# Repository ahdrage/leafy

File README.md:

# Leafy — DIY Wi-Fi Climate Controller for Nissan Leaf

**A DIY Nissan Leaf climate On/Off controller for home Wi-Fi.**

Leafy combines a custom ESP32-C3 board, a local web page and a printable enclosure. It requests climate operation over CAN; it does not carry or switch heater power. The intended profile is the **2013–2015 Leaf EV-CAN implementation**, subject to checking the actual vehicle and TCU configuration.

**Status: untested hardware prototype, Rev G.5 prepared for manufacture.** PCB production files and final component placement have been reviewed. Firmware builds and host tests pass, but no assembled Leafy has yet demonstrated heater control in a car. CAN transmission is disabled by default.

## Start here

| Goal | Documentation |
| --- | --- |
| Understand the project | [How it works](docs/OVERVIEW.md) |
| Build one | [Build guide](docs/BUILD-GUIDE.md) |
| Understand the decisions | [Development history](docs/DEVELOPMENT-HISTORY.md) |
| Inspect the current circuit | [G.5 design](hardware/rev-g/README.md), [schematic PDF](hardware/rev-g/exports/schematic.pdf), [KiCad project](hardware/rev-g/leaf-heat-v7.kicad_pro) |
| Buy components | [Parts and costs](docs/PARTS-AND-COSTS.md) |
| Order the PCB / partial assembly | [G.5 order guide](hardware/rev-g/ORDER-G5.md) |
| Build or test firmware | [Firmware instructions](firmware/leaf-heat/README.md) |
| Print the case | [Blender and STL files](enclosure/rev-g-v2/README.md) |
| Check the evidence | [Validation status](docs/VALIDATION.md) |

## Deliberately small scope

- **Heat on / Heat off** from a browser on the same home network.
- Wi-Fi only, external antenna, no SIM, subscription or cloud service.
- One CAN channel and the specified Nissan OVMS cable pinout.
- A 100 × 100 mm, four-layer PCB with generous hand-solder spacing.
- Factory assembly of **U1/U2/U4/U5/U6/L1**; **49 other components per board** are hand-soldered and the antenna plugs in.
- Independent low-battery cutoff, input damping and protected power/CAN interfaces.

Normal operation keeps Wi-Fi associated and retries after outages. **Battery protection cuts the board's power when voltage is too low**, so it becomes unreachable until the supply recovers. Availability also depends on the router and signal. Parked current and real-world reliability still need measurement.

The commands request the vehicle's climate function, not a particular heater element or temperature setpoint. The page reports requests, not independently verified heating.

## Thanks to OVMS

Leafy was inspired by the [Open Vehicle Monitoring System (OVMS)](https://www.openvehicles.com/). Its narrow Leaf wake-up and climate-command sequence is **derived from the OVMS Nissan Leaf implementation**, pinned to revision `85074a0ae7a983b308c6e2e081185492527ee073`.

Thank you to the OVMS authors and contributors for making this work available. The original MIT notice is retained in [OVMS-NOTICE.txt](firmware/leaf-heat/OVMS-NOTICE.txt). [Credits and provenance](CREDITS.md) explain the relationship and other sources. Leafy is an independent prototype, with no claimed OVMS or Nissan endorsement.

## Repository map

- `hardware/rev-g/`: current G.5 CAD, BOMs, manufacturing files, reviews and audit tools. The internal filename `leaf-heat-v7` is intentional.
- `firmware/leaf-heat/`: ESP-IDF firmware, settings template and 25 host tests.
- `enclosure/rev-g-v2/`: Blender source, STLs, renders and G.5 compatibility. Case renders retain their G.3 artwork provenance.
- `docs/`: project history, construction, costs, validation and publication notes.
- Earlier revisions and research: development history, **not current manufacturing instructions**. Always use matching G.5 files.

The public snapshot excludes personal supplier records, credentials, configured firmware images, downloaded toolchains and unrelated projects. Originals remain local. See [publication scope](docs/PUBLICATION.md).

## Licences

See [LICENSE.md](LICENSE.md) for the project licence boundaries and retained third-party notices.

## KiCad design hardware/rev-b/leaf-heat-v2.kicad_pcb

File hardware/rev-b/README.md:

> **Historical development record.** The current release is [Leafy G.5](../../README.md). Use this file for context, not current ordering or wiring instructions.

# Leaf Heat — Rev B

**Current engineering design. Four layers, 65 × 50 mm, 47 components. Not yet released for manufacture or vehicle installation.**

Open [leaf-heat-v2.kicad_pro](leaf-heat-v2.kicad_pro) in KiCad 10, then open PCB Editor. This revision replaces the two-layer Rev A layout. The circuit and heater-control purpose are unchanged; USB nets have been renamed to identify the differential pairs.

The board receives a command over home Wi-Fi and communicates with the Leaf through CAN. It does not carry heater power. Firmware, an enclosure and a tested Nissan ZE0 cable are still required.

## See the copper

Select **In1.Cu** in the PCB Editor's Layers panel and use **Show filled areas in zones**. Press **B** to refill after edits. That layer is the ground reference; there are no routed tracks on it. Copper is intentionally absent below the antenna and around non-ground holes/vias.

- [Top copper and components](exports/top.png)
- [Dedicated ground layer](exports/ground.png)
- [Internal power layer](exports/power.png)
- [Bottom copper](exports/bottom.png)
- [Component placement drawing](exports/placement.png)

## What changed

- Ground now has a dedicated internal layer plus connected surface copper. There are 87 separate ground vias, in addition to the thermal holes incorporated into footprints.
- Supply distribution uses copper areas and the internal power layer. Short, deliberately sized tracks still connect local parts.
- The regulator's bypass, bootstrap, local supply and feedback components have been regrouped. The feedback sense route comes from the output capacitor bank and stays away from the switching node.
- USB uses a parallel pair, short protection-device connections and resistors close to the controller. Both main copper paths measure approximately 40.991 mm. The main connector-to-controller paths have no vias; the USB-C duplicated-contact bridges have four local data vias and nearby ground return vias.
- Trace widths are selected by purpose. Making every trace the same width would make this design worse.

Read the [point-by-point review](LAYOUT-REVIEW.md) for the evidence and remaining limitations.

## Verification

KiCad 10.0.6 reports **0 electrical-rule violations, 0 layout-rule violations, 0 unconnected items and 0 schematic mismatches**. No DRC exclusions were added. The separate geometry audit confirms ground beneath the main USB route, matched copper lengths, main-pair spacing and no routed tracks on either internal layer.

The USB target is **90 Ω differential ±10%**. The proposed 0.25 mm traces and 0.15 mm gap calculate to **95.62 Ω in KiCad's uncoated coupled-microstrip model**. The actual solder mask, etched copper and factory stackup must be checked by the manufacturer before production. This is not measured impedance.

## Files for review

The native project, schematic, board, `.kicad_dru`, local symbols and local footprints must stay together. [BOM](exports/BOM-PCBWay.csv) and [placement coordinates](exports/placements.csv) are updated for Rev B. `exports/fabrication-review/` contains all four copper layers and drill files. See [manufacturing notes](MANUFACTURING-NOTES.md).

The existing PCBWay price was for Rev A. **It is not a price for this four-layer board.** Ordering remains paused while the design is reviewed. A four-layer board can cost more; it adds no components or wiring to the finished box.

This review does not demonstrate USB operation, power stability, parked-battery consumption, automotive transient immunity or successful heater control. Those require an assembled prototype and the bench/vehicle checks in [LAYOUT-REVIEW.md](LAYOUT-REVIEW.md). The earlier development-board plan uses different pin assignments.

## Custom-board firmware connections

| Signal | ESP32-C3 GPIO | Notes |
|---|---:|---|
| CAN TX / RX | 4 / 5 | Internal TWAI controller; intended Leaf profile 500 kbit/s |
| CAN standby | 1 | High = standby, pulled high by R10 |
| Battery sense | 0 | ADC; VPWR × 47/1047, measured after input diode |
| USB presence | 3 | ADC; half VBUS, use hysteresis |
| Status LED | 7 | High lights LED |
| USB D− / D+ | 18 / 19 | Native programming interface |
| Boot straps | 2, 8, 9 | Pulled high; BOOT button pulls GPIO9 low |

Start firmware with CAN in standby. Do not replay a heat request after reset. Implement a stop deadline, bus-error handling and a tested low-battery sleep policy. There is no independent hardware battery cutoff. USB and vehicle grounds are common; disconnect the vehicle during initial bench programming.

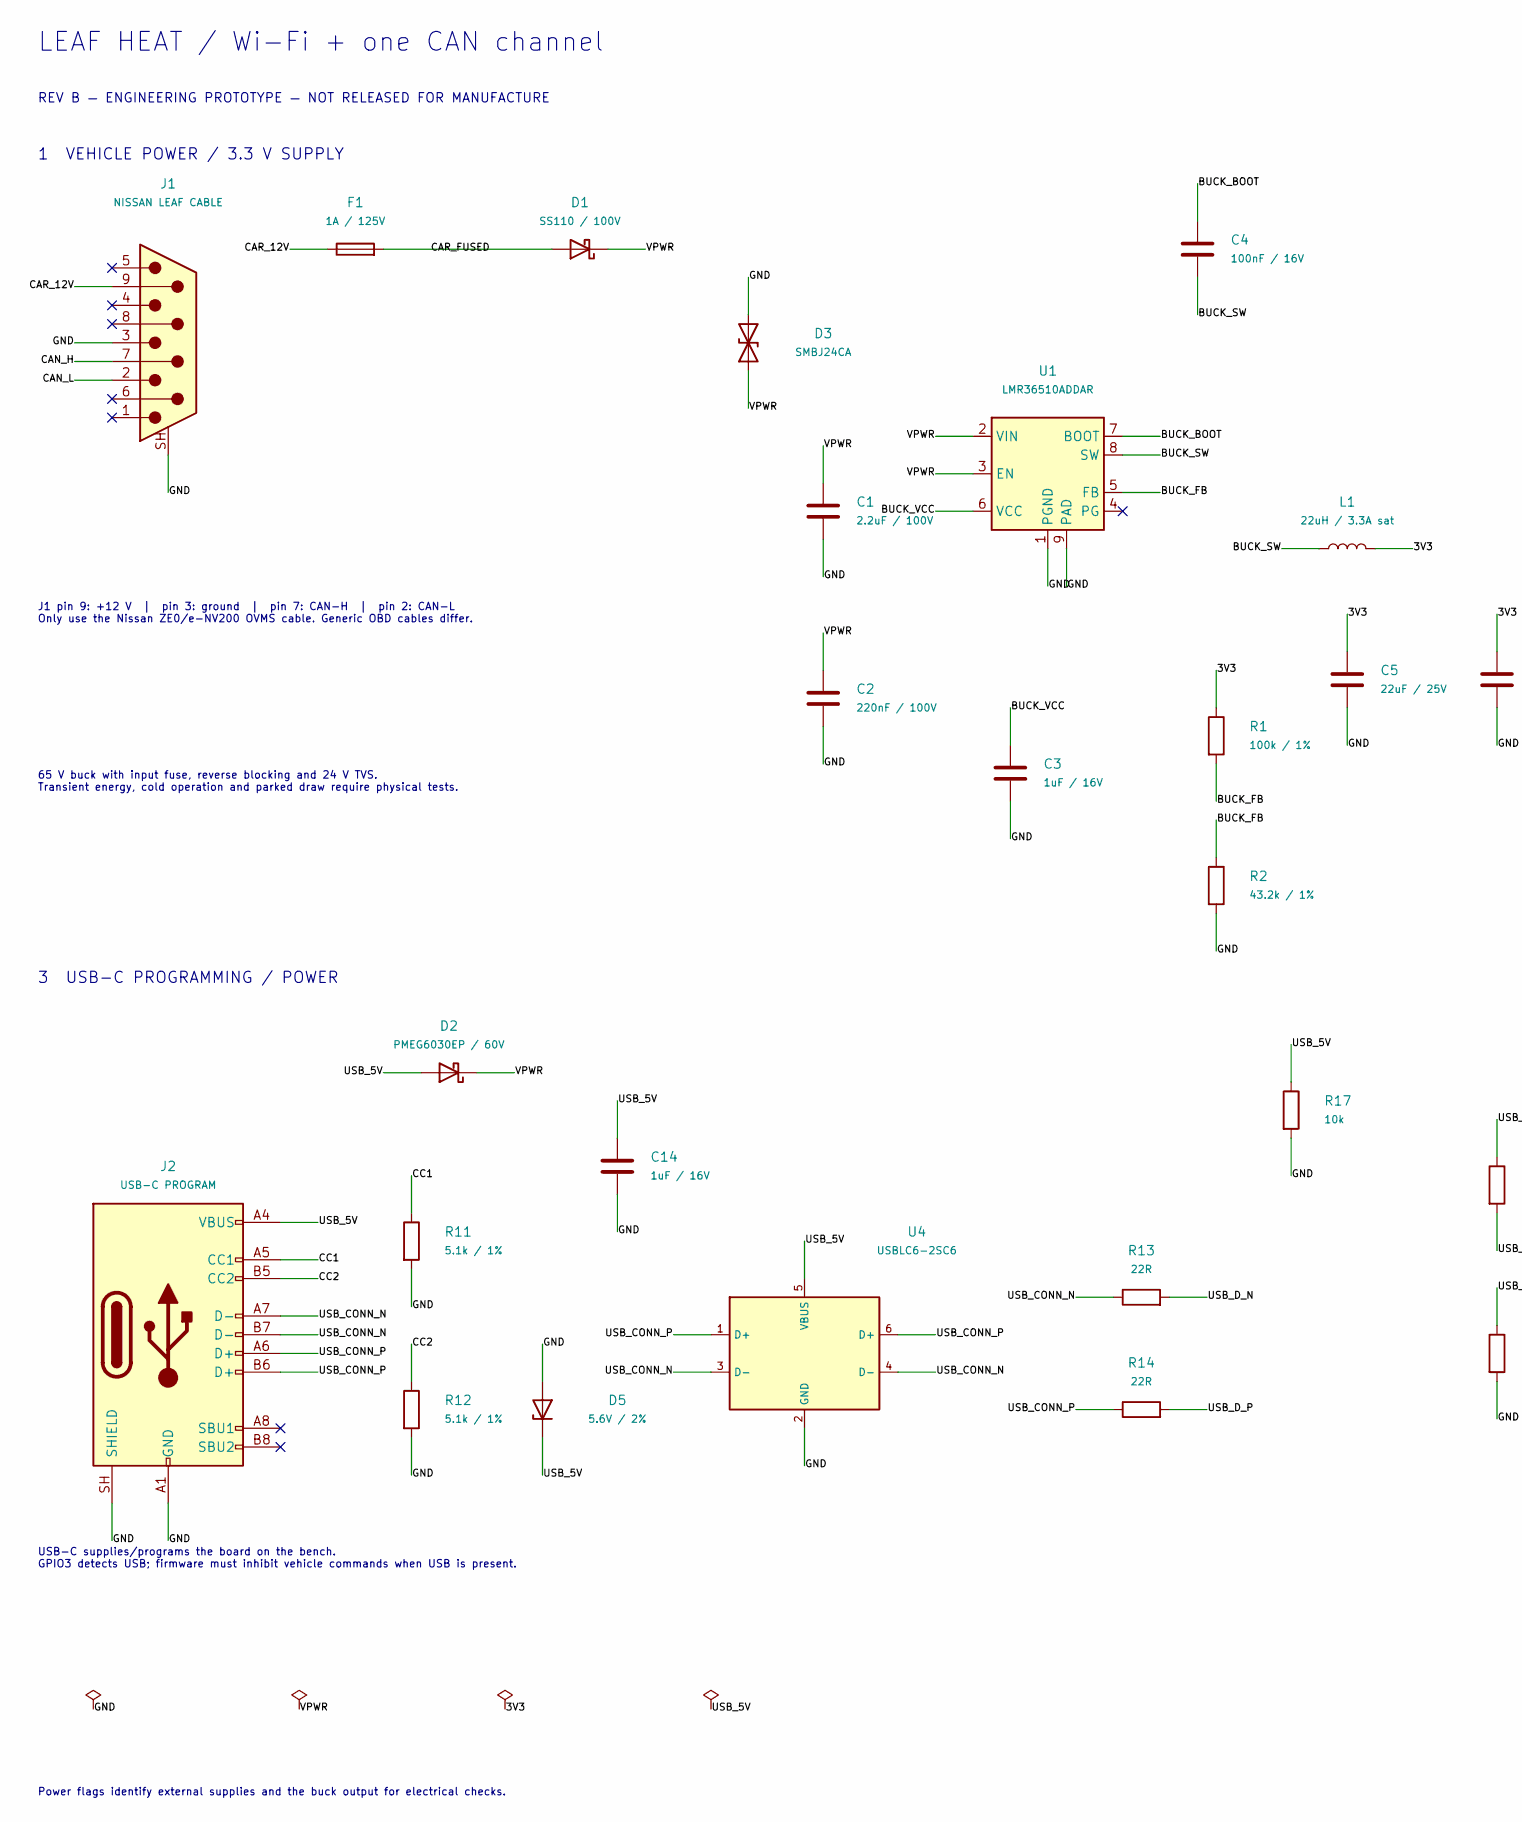
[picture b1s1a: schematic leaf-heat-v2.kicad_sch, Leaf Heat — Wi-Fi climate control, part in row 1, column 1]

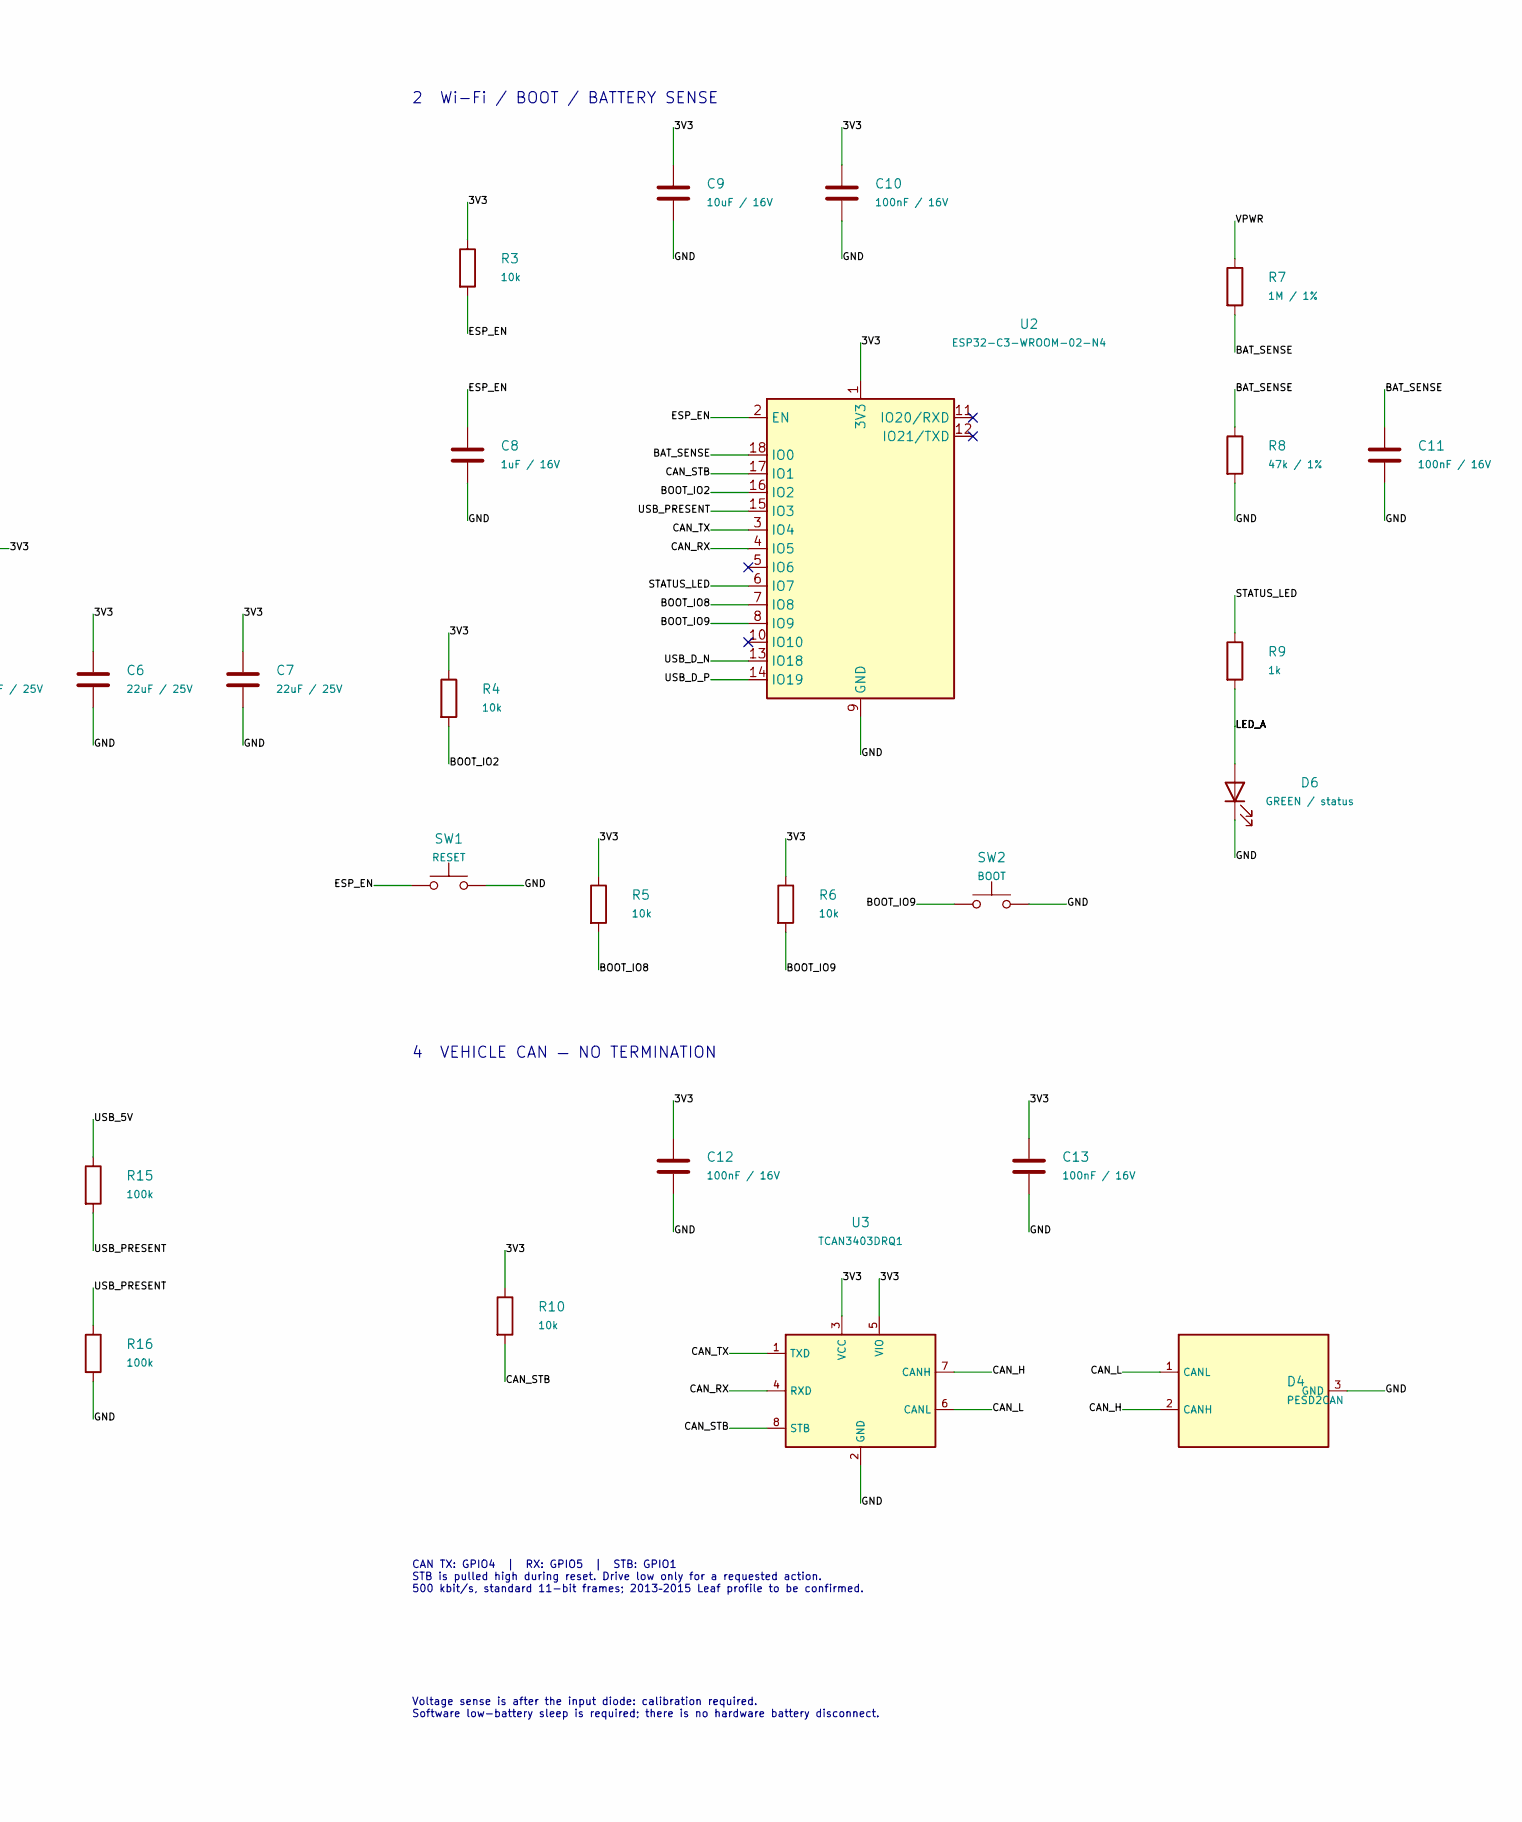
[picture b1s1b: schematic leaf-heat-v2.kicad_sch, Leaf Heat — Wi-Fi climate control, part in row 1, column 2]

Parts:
C1: 2.2uF / 100V; C_1210_3225Metric; MPN GRM32ER72A225KA35L
C2: 220nF / 100V; C_0805_2012Metric; MPN GRM21BR72A224KAC4L
C3, C8, C14: 1uF / 16V; C_0603_1608Metric; MPN GRM188R71C105KA12D
C4, C10, C11, C12, C13: 100nF / 16V; C_0603_1608Metric; MPN GRM188R71C104KA01D
C5, C6, C7: 22uF / 25V; C_1210_3225Metric; MPN GRM32ER71E226KE15L
C9: 10uF / 16V; C_0805_2012Metric; MPN GRM21BR71C106KE51L
D1: SS110 / 100V; D_SMA; MPN SS110-13-F
D2: PMEG6030EP / 60V; D_SOD-128; MPN PMEG6030EP,115
D3: SMBJ24CA; D_SMB; MPN SMBJ24CA
D4: PESD2CAN; SOT-23; MPN PESD2CAN,215
D5: 5.6V / 2%; D_SOD-123; MPN BZT52-B5V6X
D6: GREEN / status; LED_0603_1608Metric; MPN LTST-C190KGKT
F1: 1A / 125V; Fuse_Littelfuse-NANO2-451_453; MPN 0451001.MRL
J1: NISSAN LEAF CABLE; NorComp_182-009-113R531; MPN 182-009-113R531
J2: USB-C PROGRAM; USB_C_Receptacle_GCT_USB4105-xx-A_16P_TopMnt_Horizontal; MPN USB4105-GF-A
L1: 22uH / 3.3A sat; L_Bourns_SRN6045TA; MPN SRN6045TA-220M
R1: 100k / 1%; R_0603_1608Metric; MPN RC0603FR-07100KL
R2: 43.2k / 1%; R_0603_1608Metric; MPN RC0603FR-0743K2L
R3, R4, R5, R6, R10, R17: 10k; R_0603_1608Metric; MPN RC0603FR-0710KL
R7: 1M / 1%; R_0603_1608Metric; MPN RC0603FR-071ML
R8: 47k / 1%; R_0603_1608Metric; MPN RC0603FR-0747KL
R9: 1k; R_0603_1608Metric; MPN RC0603FR-071KL
R11, R12: 5.1k / 1%; R_0603_1608Metric; MPN RC0603FR-075K1L
R13, R14: 22R; R_0603_1608Metric; MPN RC0603FR-0722RL
R15, R16: 100k; R_0603_1608Metric; MPN RC0603FR-07100KL
SW1: RESET; SW_SPST_TL3342; MPN TL3342F160QG
SW2: BOOT; SW_SPST_TL3342; MPN TL3342F160QG
U1: LMR36510ADDAR; Texas_HTSOP-8-1EP_3.9x4.9mm_P1.27mm_EP2.95x4.9mm_Mask2.4x3.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; MPN LMR36510ADDAR
U2: ESP32-C3-WROOM-02-N4; ESP32-C3-WROOM-02_0p3mm_Vias; MPN ESP32-C3-WROOM-02-N4
U3: TCAN3403DRQ1; SOIC-8_3.9x4.9mm_P1.27mm; MPN TCAN3403DRQ1
U4: USBLC6-2SC6; SOT-23-6; MPN USBLC6-2SC6

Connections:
/3V3: C5.1, C6.1, C7.1, C9.1, C10.1, C12.1, C13.1, L1.2, R1.1, R3.1, R4.1, R5.1, R6.1, R10.1, U2.1 (3V3), U3.3 (VCC), U3.5 (VIO)
/BAT_SENSE: C11.1, R7.2, R8.1, U2.18 (IO0)
/BOOT_IO2: R4.2, U2.16 (IO2)
/BOOT_IO8: R5.2, U2.7 (IO8)
/BOOT_IO9: R6.2, SW2.1, U2.8 (IO9)
/BUCK_BOOT: C4.1, U1.7 (BOOT)
/BUCK_FB: R1.2, R2.1, U1.5 (FB)
/BUCK_SW: C4.2, L1.1, U1.8 (SW)
/BUCK_VCC: C3.1, U1.6 (VCC)
/CAN_H: D4.2 (CANH), J1.7, U3.7 (CANH)
/CAN_L: D4.1 (CANL), J1.2, U3.6 (CANL)
/CAN_RX: U2.4 (IO5), U3.4 (RXD)
/CAN_STB: R10.2, U2.17 (IO1), U3.8 (STB)
/CAN_TX: U2.3 (IO4), U3.1 (TXD)
/CAR_12V: F1.1, J1.9
/CAR_FUSED: D1.2 (A), F1.2
/CC1: J2.A5 (CC1), R11.1
/CC2: J2.B5 (CC2), R12.1
/ESP_EN: C8.1, R3.2, SW1.1, U2.2 (EN)
/GND: C1.2, C2.2, C3.2, C5.2, C6.2, C7.2, C8.2, C9.2, C10.2, C11.2, C12.2, C13.2, C14.2, D3.2 (A2), D4.3 (GND), D5.2 (A), D6.1 (K), J1.3, J1.SH (PAD), J2.A1 (GND), J2.A12 (GND), J2.B1 (GND), J2.B12 (GND), J2.SH (SHIELD), R2.2, R8.2, R11.2, R12.2, R16.2, R17.2, SW1.2, SW2.2, U1.1 (PGND), U1.9 (PAD), U2.9 (GND), U2.19 (GND), U3.2 (GND), U4.2 (GND)
/LED_A: D6.2 (A), R9.2
/STATUS_LED: R9.1, U2.6 (IO7)
/USB_5V: C14.1, D2.2 (A), D5.1 (K), J2.A4 (VBUS), J2.A9 (VBUS), J2.B4 (VBUS), J2.B9 (VBUS), R15.1, R17.1, U4.5 (VBUS)
/USB_CONN_N: J2.A7 (D-), J2.B7 (D-), R13.1, U4.3 (D-), U4.4 (D-)
/USB_CONN_P: J2.A6 (D+), J2.B6 (D+), R14.1, U4.1 (D+), U4.6 (D+)
/USB_D_N: R13.2, U2.13 (IO18)
/USB_D_P: R14.2, U2.14 (IO19)
/USB_PRESENT: R15.2, R16.1, U2.15 (IO3)
/VPWR: C1.1, C2.1, D1.1 (K), D2.1 (K), D3.1 (A1), R7.1, U1.2 (VIN), U1.3 (EN)

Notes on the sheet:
LEAF HEAT / Wi-Fi + one CAN channel
REV B — ENGINEERING PROTOTYPE — NOT RELEASED FOR MANUFACTURE
1 VEHICLE POWER / 3.3 V SUPPLY
2 Wi-Fi / BOOT / BATTERY SENSE
3 USB-C PROGRAMMING / POWER
4 VEHICLE CAN — NO TERMINATION
J1 pin 9: +12 V | pin 3: ground | pin 7: CAN-H | pin 2: CAN-L Only use the Nissan ZE0/e-NV200 OVMS cable. Generic OBD cables differ.
65 V buck with input fuse, reverse blocking and 24 V TVS. Transient energy, cold operation and parked draw require physical tests.
USB-C supplies/programs the board on the bench. GPIO3 detects USB; firmware must inhibit vehicle commands when USB is present.
CAN TX: GPIO4 | RX: GPIO5 | STB: GPIO1 STB is pulled high during reset. Drive low only for a requested action. 500 kbit/s, standard 11-bit frames; 2013–2015 Leaf profile to be confirmed.
Voltage sense is after the input diode: calibration required. Software low-battery sleep is required; there is no hardware battery disconnect.
Power flags identify external supplies and the buck output for electrical checks.

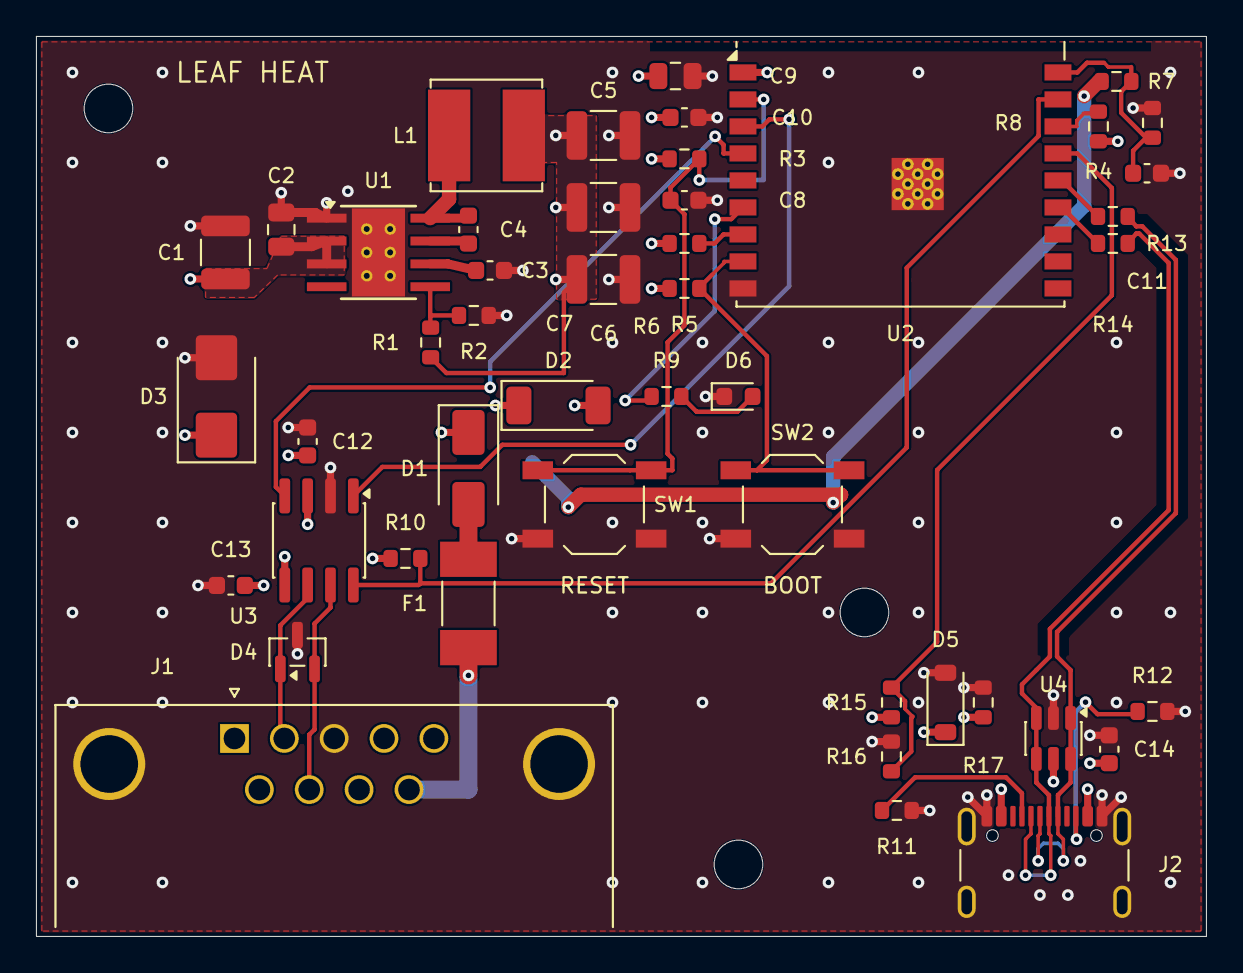
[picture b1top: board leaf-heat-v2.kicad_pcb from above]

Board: 4 copper layers, 65.0 x 50.0 mm, 50 parts (0 on the bottom side), 29 nets.

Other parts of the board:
H1, H2, H3: MountingHole_2.7mm_M2.5

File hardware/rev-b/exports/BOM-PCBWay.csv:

Item,Designator,Quantity,Manufacturer,Manufacturer Part Number,Description / Value,Footprint,Notes
1,J1,1,NorComp,182-009-113R531,NISSAN LEAF CABLE,Leaf:NorComp_182-009-113R531,Male DB9; only the specified Nissan OVMS cable pinout. Shell grounded. Mechanical mating review required.
2,F1,1,Littelfuse,0451001.MRL,1A / 125V,Fuse:Fuse_Littelfuse-NANO2-451_453,
3,D1,1,Diodes Incorporated,SS110-13-F,SS110 / 100V,Diode_SMD:D_SMA,
4,D3,1,Littelfuse,SMBJ24CA,SMBJ24CA,Diode_SMD:D_SMB,
5,U1,1,Texas Instruments,LMR36510ADDAR,LMR36510ADDAR,Package_SO:Texas_HTSOP-8-1EP_3.9x4.9mm_P1.27mm_EP2.95x4.9mm_Mask2.4x3.1mm_ThermalVias,
6,C1,1,Murata,GRM32ER72A225KA35L,2.2uF / 100V,Capacitor_SMD:C_1210_3225Metric,
7,C2,1,Murata,GRM21BR72A224KAC4L,220nF / 100V,Capacitor_SMD:C_0805_2012Metric,
8,"C3,C8,C14",3,Murata,GRM188R71C105KA12D,1uF / 16V,Capacitor_SMD:C_0603_1608Metric,
9,"C4,C10,C11,C12,C13",5,Murata,GRM188R71C104KA01D,100nF / 16V,Capacitor_SMD:C_0603_1608Metric,
10,L1,1,Bourns,SRN6045TA-220M,22uH / 3.3A sat,Inductor_SMD:L_Bourns_SRN6045TA,
11,"C5,C6,C7",3,Murata,GRM32ER71E226KE15L,22uF / 25V,Capacitor_SMD:C_1210_3225Metric,
12,"R1,R15,R16",3,Yageo,RC0603FR-07100KL,100k / 1%,Resistor_SMD:R_0603_1608Metric,
13,R2,1,Yageo,RC0603FR-0743K2L,43.2k / 1%,Resistor_SMD:R_0603_1608Metric,
14,U2,1,Espressif,ESP32-C3-WROOM-02-N4,ESP32-C3-WROOM-02-N4,Leaf:ESP32-C3-WROOM-02_0p3mm_Vias,
15,"R3,R4,R5,R6,R10,R17",6,Yageo,RC0603FR-0710KL,10k,Resistor_SMD:R_0603_1608Metric,
16,C9,1,Murata,GRM21BR71C106KE51L,10uF / 16V,Capacitor_SMD:C_0805_2012Metric,
17,"SW1,SW2",2,E-Switch,TL3342F160QG,RESET,Button_Switch_SMD:SW_SPST_TL3342,
18,R7,1,Yageo,RC0603FR-071ML,1M / 1%,Resistor_SMD:R_0603_1608Metric,
19,R8,1,Yageo,RC0603FR-0747KL,47k / 1%,Resistor_SMD:R_0603_1608Metric,
20,R9,1,Yageo,RC0603FR-071KL,1k,Resistor_SMD:R_0603_1608Metric,
21,D6,1,Lite-On,LTST-C190KGKT,GREEN / status,LED_SMD:LED_0603_1608Metric,
22,U3,1,Texas Instruments,TCAN3403DRQ1,TCAN3403DRQ1,Package_SO:SOIC-8_3.9x4.9mm_P1.27mm,
23,D4,1,Nexperia,"PESD2CAN,215",PESD2CAN,Package_TO_SOT_SMD:SOT-23,
24,J2,1,GCT,USB4105-GF-A,USB-C PROGRAM,Connector_USB:USB_C_Receptacle_GCT_USB4105-xx-A_16P_TopMnt_Horizontal,
25,"R11,R12",2,Yageo,RC0603FR-075K1L,5.1k / 1%,Resistor_SMD:R_0603_1608Metric,
26,D2,1,Nexperia,"PMEG6030EP,115",PMEG6030EP / 60V,Diode_SMD:D_SOD-128,Low-drop USB blocking diode; qualify USB startup at minimum VBUS.
27,U4,1,STMicroelectronics,USBLC6-2SC6,USBLC6-2SC6,Package_TO_SOT_SMD:SOT-23-6,
28,"R13,R14",2,Yageo,RC0603FR-0722RL,22R,Resistor_SMD:R_0603_1608Metric,
29,D5,1,Nexperia,BZT52-B5V6X,5.6V / 2%,Diode_SMD:D_SOD-123,Limits USB rail rise from the reverse leakage of D2 when car-powered; R17 discharges the rail.

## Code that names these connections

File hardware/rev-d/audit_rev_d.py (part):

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drc=json.loads((E/'drc-final.json').read_text());check(all(not drc[k] for k in ['violations','unconnected_items','schematic_parity']),'Native DRC, connectivity and schematic parity all pass')
erc=json.loads((E/'erc.json').read_text());check(not any(s.get('violations') for s in erc.get('sheets',[])),'Native ERC passes')
def net(r,n):return pins[(r,str(n))].lstrip('/')
check([net('J1',n) for n in [9,3,7,2]]==['CAR_12V','GND','CAN_H','CAN_L'],'Nissan DB9 pinout retained')
check([net('J3',n) for n in [1,2,3]]==['GND','PROG_RX','PROG_TX'],'UART header exposes no supply pin')
check([net('U2',n) for n in [3,4,7,8,11,12,17]]==['CAN_TX','CAN_RX','BOOT_IO8','BOOT_IO9','UART_RX','UART_TX','CAN_STB'],'Firmware GPIO assignments retained')
check(not any({q['nets'].get('1'),q['nets'].get('2')}=={'CAN_H','CAN_L'} and q['ref'].startswith('R') for q in parts),'No CAN termination resistor added')
vnom=1+100/43.2;vmin=.985*(1+100*.99/(43.2*1.01));vmax=1.015*(1+100*1.01/(43.2*.99));adc=65*47*1.01/(1000*.99+47*1.01)
check(3<vmin<vnom<vmax<3.6,'Static feedback/reference tolerance range remains within MCU/CAN supply limits')
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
